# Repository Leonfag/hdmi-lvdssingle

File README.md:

# hdmi-lvdssingle
single hdmi to lvds board based on watterotts approach

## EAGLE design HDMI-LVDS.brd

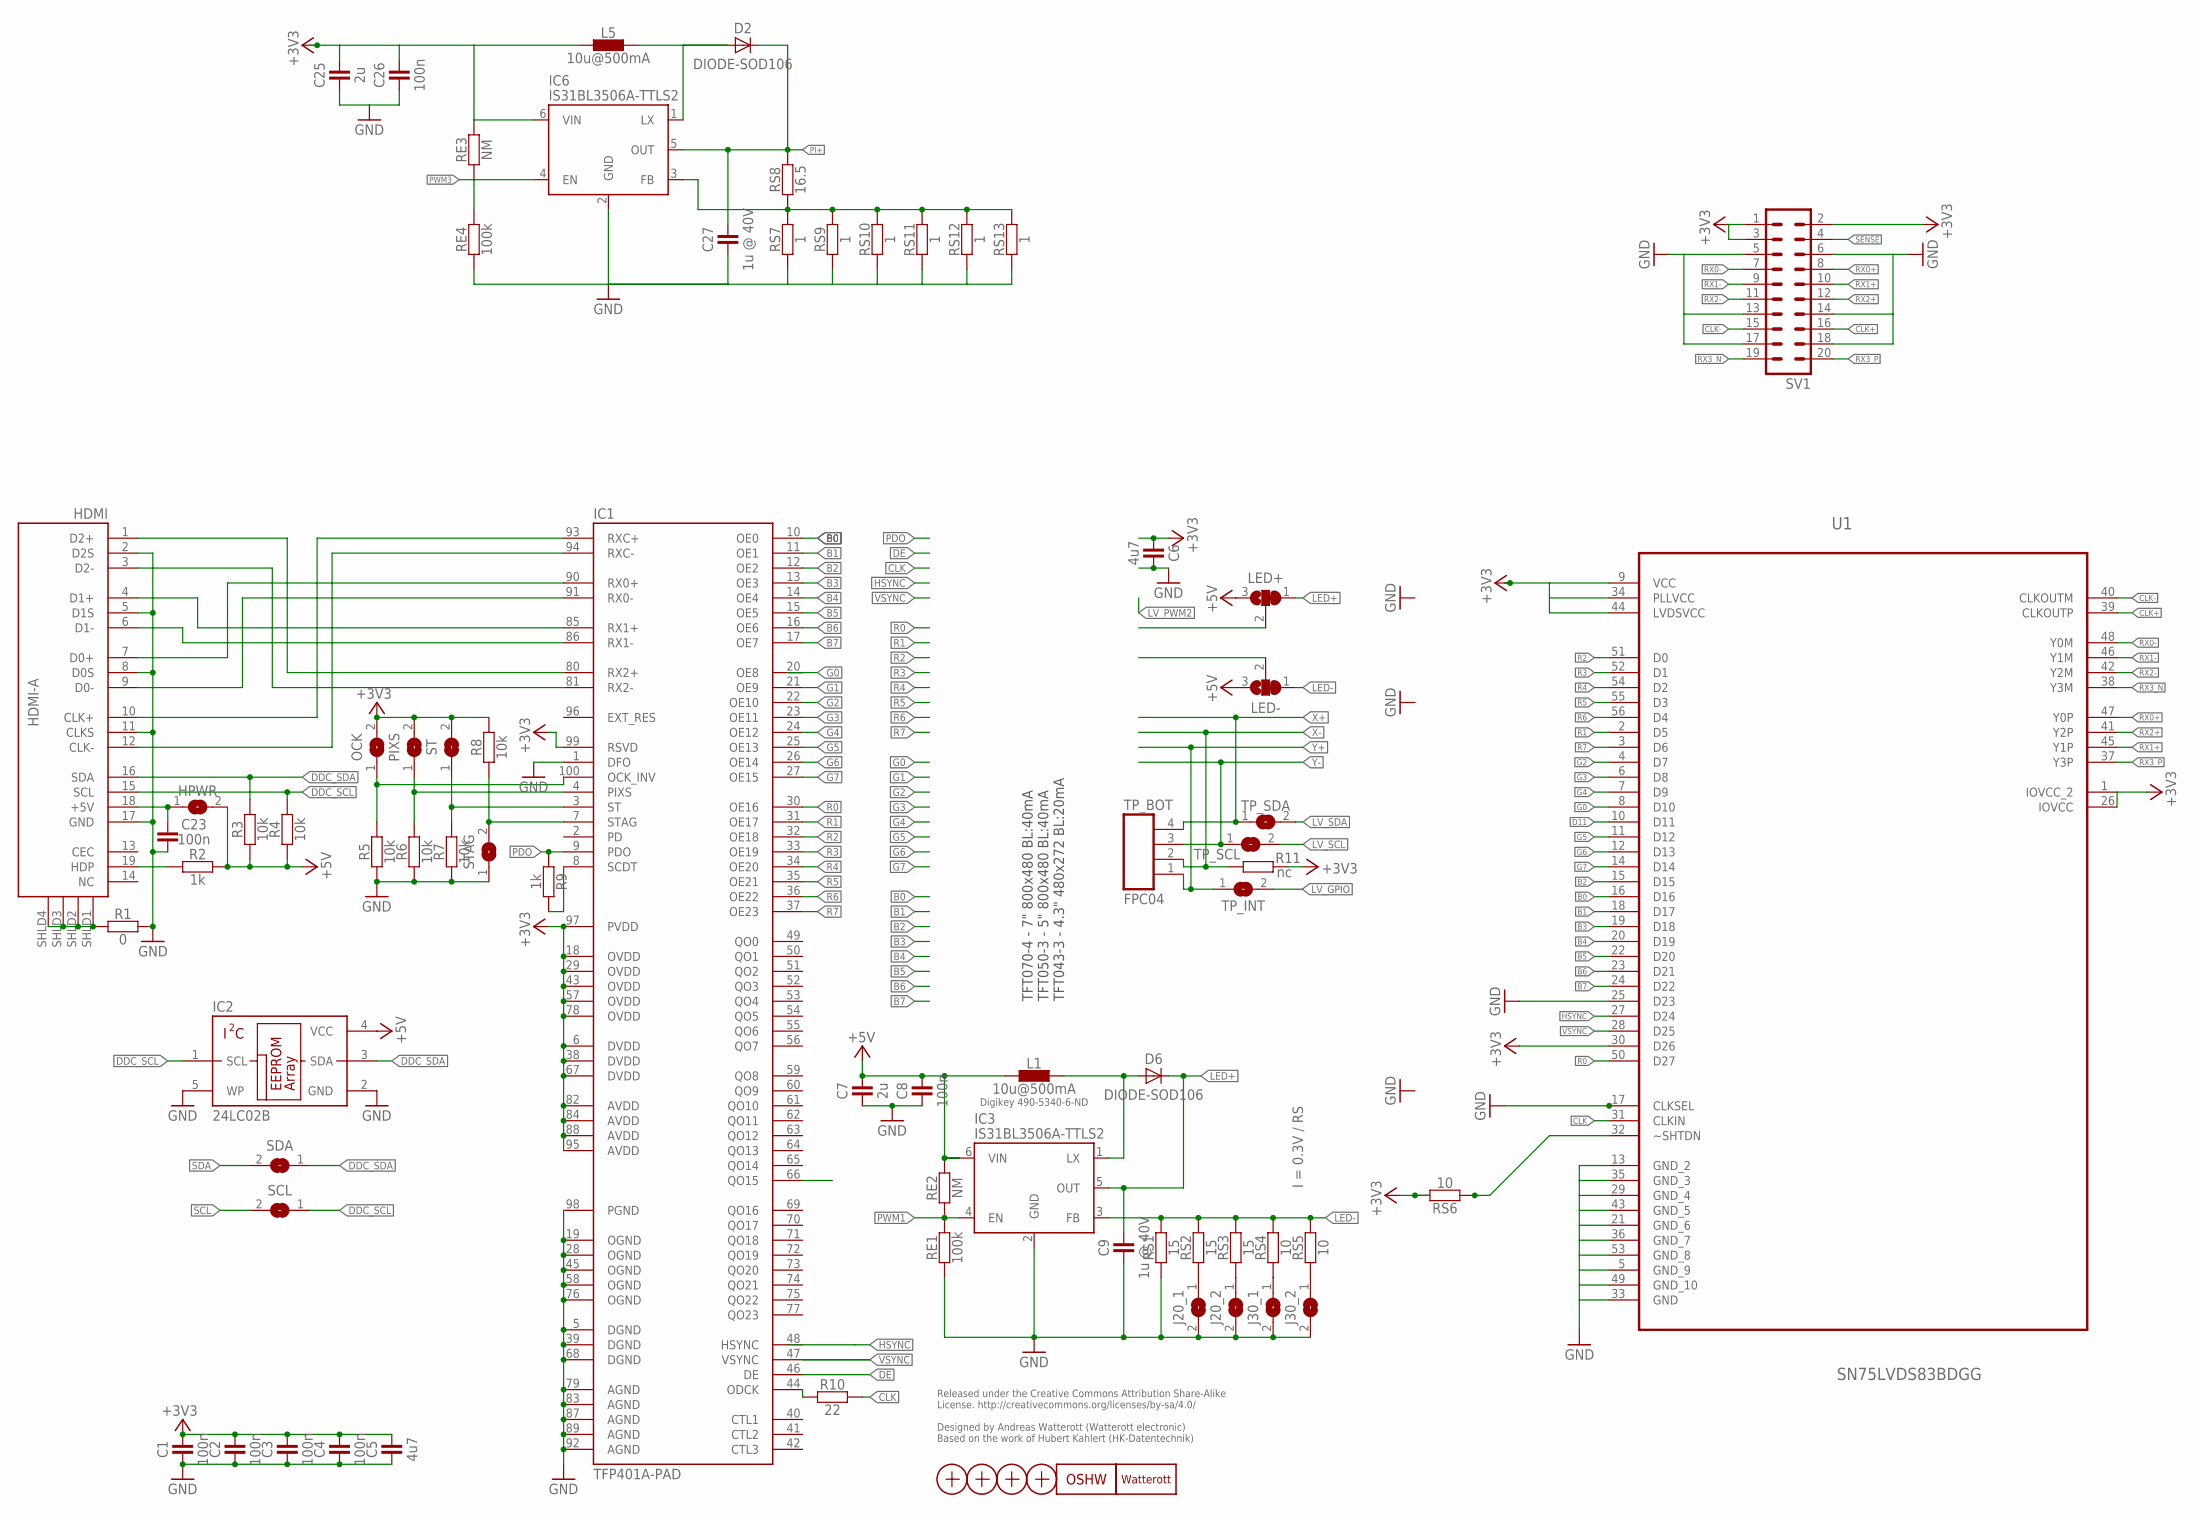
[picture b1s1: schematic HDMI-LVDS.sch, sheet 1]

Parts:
C1, C2, C3, C4, C8, C23, C26: 100n; C0402
C5, C6: 4u7; C0402
C7, C25: 2u; C0402
C9, C27: 1u @ 40V; C0805
D2, D6: DIODE-SOD106; SOD106
HDMI: HDMI-A; HDMI_10029449
HPWR: JUMPER2-0402
IC1: TFP401A-PAD; TQFP100-PAD
IC2: 24LC02B; SOT23-5
IC3, IC6: IS31BL3506A-TTLS2; SOT23-6
J20_1, J20_2, J30_1, J30_2: JUMPER2-0402
L1, L5: 10u@500mA; L_1212
LED+: JUMPER3-0402
LED-: JUMPER3-0402
LOGO1: OSHW_LOGOX0070; OSHW_6X70
LOGO3: LOGO-S_PLACE_S; SPARK_TPLACE_S
OCK: JUMPER2-0201-NC; JUMPER2-0201_NC
PIXS: JUMPER2-0201-NC; JUMPER2-0201_NC
R1: 0; C0402
R2, R9: 1k; C0402
R3, R4, R5, R6, R7, R8: 10k; C0402
R10: 22; C0402
R11: nc; C0402
RE1, RE4: 100k; C0402
RE2, RE3: NM; C0402
RS1, RS2, RS3: 15; C0402
RS4, RS5, RS6: 10; C0402
RS7, RS9, RS10, RS11, RS12, RS13: 1; C0402
RS8: 16.5; C0402
SCL: JUMPER2-0402
SDA: JUMPER2-0402
ST: JUMPER2-0201-NC; JUMPER2-0201_NC
STAG: JUMPER2-0201-NC; JUMPER2-0201_NC
SV1: MA10-2
TP_BOT: FPC04
TP_INT: JUMPER2-0402
TP_SCL: JUMPER2-0402
TP_SDA: JUMPER2-0402
U1: SN75LVDS83BDGG; SOP50P810X120-56N
X1, X2, X3, X4: PASSER-07; PASSER_07MM

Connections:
+3V3: C1.2, C2.2, C3.2, C4.2, C5.2, C6.1, C25.2, C26.2, IC1.6 (DVDD), IC1.18 (OVDD), IC1.29 (OVDD), IC1.38 (DVDD), IC1.43 (OVDD), IC1.57 (OVDD), IC1.67 (DVDD), IC1.78 (OVDD), IC1.82 (AVDD), IC1.84 (AVDD), IC1.88 (AVDD), IC1.95 (AVDD), IC1.97 (PVDD), IC1.99 (RSVD), IC6.6 (VIN), L5.1, OCK.2, PIXS.2, R8.2, R11.2, RE3.2, RS6.2, ST.2, SV1.1, SV1.2, SV1.3, U1.1 (IOVCC_2), U1.9 (VCC), U1.26 (IOVCC), U1.30 (D26), U1.34 (PLLVCC), U1.44 (LVDSVCC); also elsewhere on the board
+5V: C7.2, C8.2, HPWR.2, IC2.4 (VCC), IC3.6 (VIN), L1.1, LED+.3, LED-.3, R2.2, R3.1, R4.1, RE2.2; also elsewhere on the board
B0: IC1.10 (OE0), U1.16 (D16)
B1: IC1.11 (OE1), U1.18 (D17)
B2: IC1.12 (OE2), U1.15 (D15)
B3: IC1.13 (OE3), U1.19 (D18)
B4: IC1.14 (OE4), U1.20 (D19)
B5: IC1.15 (OE5), U1.22 (D20)
B6: IC1.16 (OE6), U1.23 (D21)
B7: IC1.17 (OE7), U1.24 (D22)
CLK: R10.2, U1.31 (CLKIN)
CLK+: SV1.16, U1.39 (CLKOUTP)
CLK-: SV1.15, U1.40 (CLKOUTM)
CLK_N: HDMI.12 (CLK-), IC1.94 (RXC-)
CLK_P: HDMI.10 (CLK+), IC1.93 (RXC+)
D0_N: HDMI.9 (D0-), IC1.91 (RX0-)
D0_P: HDMI.7 (D0+), IC1.90 (RX0+)
D1_N: HDMI.6 (D1-), IC1.86 (RX1-)
D1_P: HDMI.4 (D1+), IC1.85 (RX1+)
D2_N: HDMI.3 (D2-), IC1.81 (RX2-)
D2_P: HDMI.1 (D2+), IC1.80 (RX2+)
D11: U1.10 (D11)
DDC_SCL: HDMI.15 (SCL), IC2.1 (SCL), R4.2, SCL.1
DDC_SDA: HDMI.16 (SDA), IC2.3 (SDA), R3.2, SDA.1
DE: IC1.46 (DE)
G0: IC1.20 (OE8), U1.8 (D10)
G1: IC1.21 (OE9)
G2: IC1.22 (OE10), U1.4 (D7)
G3: IC1.23 (OE11), U1.6 (D8)
G4: IC1.24 (OE12), U1.7 (D9)
G5: IC1.25 (OE13), U1.11 (D12)
G6: IC1.26 (OE14), U1.12 (D13)
G7: IC1.27 (OE15), U1.14 (D14)
GND: C1.1, C2.1, C3.1, C4.1, C5.1, C6.2, C7.1, C8.1, C9.1, C23.1, C25.1, C26.1, C27.1, HDMI.2 (D2S), HDMI.5 (D1S), HDMI.8 (D0S), HDMI.11 (CLKS), HDMI.17 (GND), IC1.1 (DFO), IC1.5 (DGND), IC1.19 (OGND), IC1.28 (OGND), IC1.39 (DGND), IC1.45 (OGND), IC1.58 (OGND), IC1.68 (DGND), IC1.76 (OGND), IC1.79 (AGND), IC1.83 (AGND), IC1.87 (AGND), IC1.89 (AGND), IC1.92 (AGND), IC1.98 (PGND), IC2.2 (GND), IC2.5 (WP), IC3.2 (GND), IC6.2 (GND), J20_1.2, J20_2.2, J30_1.2, J30_2.2, R1.1, R5.1, R6.1, R7.1, RE1.1, RE4.1, RS1.1, RS7.1, RS9.1, RS10.1, RS11.1, RS12.1, RS13.1, STAG.1, SV1.5, SV1.6, SV1.13, SV1.14, SV1.17, SV1.18, U1.5 (GND_9), U1.13 (GND_2), U1.21 (GND_6), U1.25 (D23), U1.29 (GND_4), U1.33 (GND), U1.35 (GND_3), U1.36 (GND_7), U1.43 (GND_5), U1.49 (GND_10), U1.53 (GND_8); also elsewhere on the board
HDMI_5V: C23.2, HDMI.18 (+5V), HPWR.1
HDMI_DECT: HDMI.19 (HDP), R2.1
HSYNC: IC1.48 (HSYNC), U1.27 (D24)
LED+: C9.2, D6.C, IC3.5 (OUT), LED+.1
LED-: IC3.3 (FB), LED-.1, RS1.2, RS2.2, RS3.2, RS4.2, RS5.2
LEDA: LED+.2
LEDC: LED-.2
LV_GPIO: TP_INT.2; also elsewhere on the board
LV_SCL: TP_SCL.2; also elsewhere on the board
LV_SDA: TP_SDA.2; also elsewhere on the board
LX: D6.A, IC3.1 (LX), L1.2
unnamed: J20_2.1, RS3.1
unnamed: IC1.44 (ODCK), R10.1
unnamed: J30_1.1, RS4.1
unnamed: J20_1.1, RS2.1
unnamed: J30_2.1, RS5.1
unnamed: IC6.3 (FB), RS7.2, RS8.1, RS9.2, RS10.2, RS11.2, RS12.2, RS13.2
unnamed: RS6.1, U1.32 (~SHTDN)
unnamed: D2.A, IC6.1 (LX), L5.2
OCKINV: IC1.100 (OCK_INV), OCK.1, R5.2
PDO: IC1.9 (PDO), R9.1
PI+: C27.2, D2.C, IC6.5 (OUT), RS8.2; also elsewhere on the board
PIXS: IC1.4 (PIXS), PIXS.1, R6.2
PWM1: IC3.4 (EN), RE1.2, RE2.1; also elsewhere on the board
PWM3: IC6.4 (EN), RE3.1, RE4.2; also elsewhere on the board
R0: IC1.30 (OE16), U1.50 (D27)
R1: IC1.31 (OE17), U1.2 (D5)
R2: IC1.32 (OE18), U1.51 (D0)
R3: IC1.33 (OE19), U1.52 (D1)
R4: IC1.34 (OE20), U1.54 (D2)
R5: IC1.35 (OE21), U1.55 (D3)
R6: IC1.36 (OE22), U1.56 (D4)
R7: IC1.37 (OE23), U1.3 (D6)
RX0+: SV1.8, U1.47 (Y0P)
RX0-: SV1.7, U1.48 (Y0M)
RX1+: SV1.10, U1.45 (Y1P)
RX1-: SV1.9, U1.46 (Y1M)
RX2+: SV1.12, U1.41 (Y2P)
RX2-: SV1.11, U1.42 (Y2M)
RX3_N: SV1.19, U1.38 (Y3M)
RX3_P: SV1.20, U1.37 (Y3P)
SCDT: IC1.8 (SCDT), R9.2
SCL: SCL.2; also elsewhere on the board
SDA: SDA.2; also elsewhere on the board
SENSE: SV1.4; also elsewhere on the board
SHLD3: HDMI.SHLD1 (SHLD), HDMI.SHLD2 (SHLD), HDMI.SHLD3 (SHLD), HDMI.SHLD4 (SHLD), R1.2
ST: IC1.3 (ST), R7.2, ST.1
STAG: IC1.7 (STAG), R8.1, STAG.2
VSYNC: IC1.47 (VSYNC), U1.28 (D25)
X+: TP_BOT.4, TP_SDA.1; also elsewhere on the board
X-: R11.1, TP_BOT.2; also elsewhere on the board
Y+: TP_BOT.1, TP_INT.1; also elsewhere on the board
Y-: TP_BOT.3, TP_SCL.1; also elsewhere on the board

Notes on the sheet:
I = 0.3V / RS
Digikey 490-5340-6-ND
Released under the Creative Commons Attribution Share-Alike License. http://creativecommons.org/licenses/by-sa/4.0/ Designed by Andreas Watterott (Watterott electronic) Based on the work of Hubert Kahlert (HK-Datentechnik)
TFT070-4 - 7" 800x480 BL:40mA TFT050-3 - 5" 800x480 BL:40mA TFT043-3 - 4.3" 480x272 BL:20mA

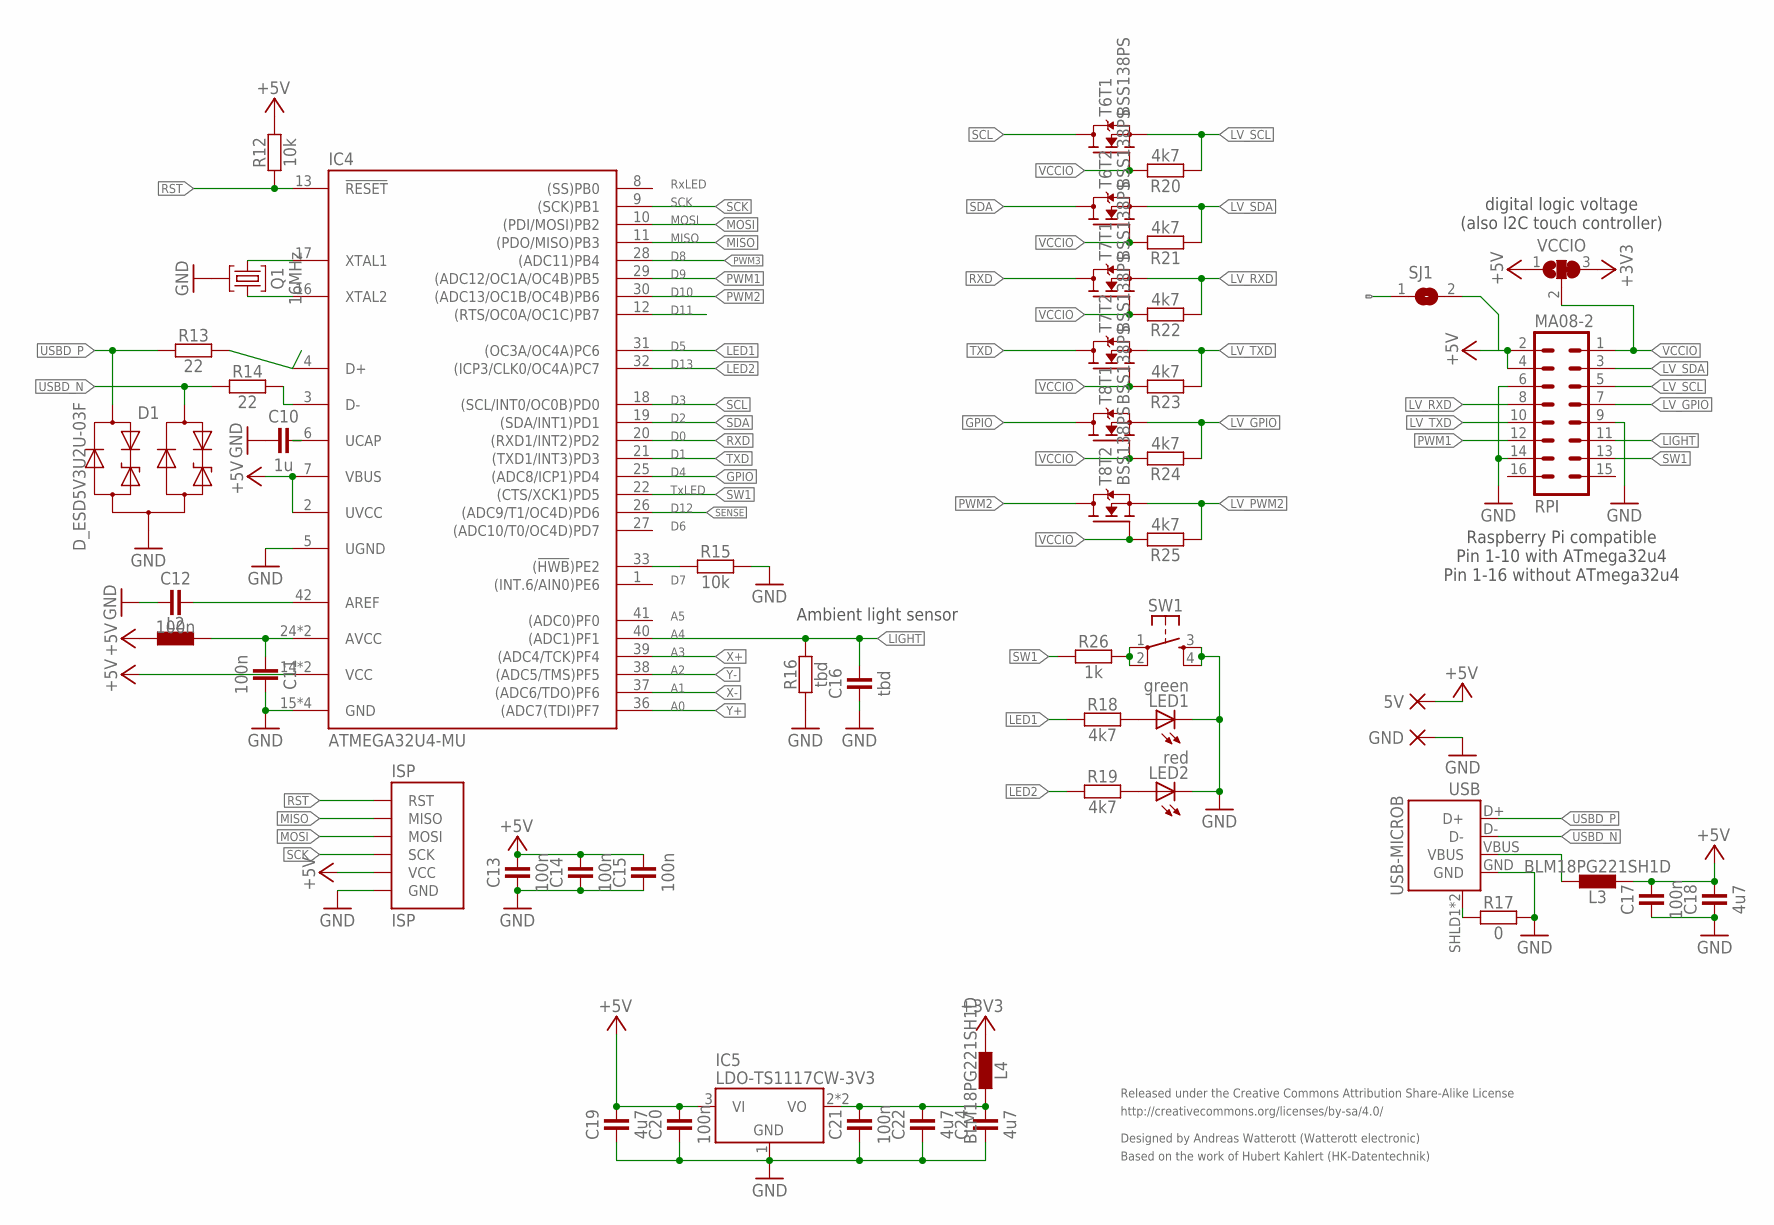
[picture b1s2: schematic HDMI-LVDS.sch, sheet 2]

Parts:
5V: PAD-1.27X2.54_NC
C10: 1u; C0402
C11, C12, C13, C14, C15, C17, C20, C21: 100n; C0402
C16: tbd; C0402
C18, C19, C22, C24: 4u7; C0402
D1: D_ESD5V3U2U-03F; SOT723
GND: PAD-1.27X2.54_NC
IC4: ATMEGA32U4-MU; QFN44
IC5: LDO-TS1117CW-3V3; SOT223
ISP: ISP; ISP-2X3
L2: INDUCTOR-0603; C0603
L3, L4: BLM18PG221SH1D; C0603
LED1: green; C0603
LED2: red; C0603
Q1: 16MHz; CRYSTAL_32X13
R12, R15: 10k; C0402
R13, R14: 22; C0402
R16: tbd; C0402
R17: 0; C0402
R18, R19, R20, R21, R22, R23, R24, R25: 4k7; C0402
R26: 1k; C0402
RPI: MA08-2
SJ1: SJ
SW1: SW-TACTILE-PTS840P; PTS840P
T6, T7, T8: BSS138PS; SOT363
USB: USB-MICROB; USB-MICROB-10103594
VCCIO: JUMPER3-0402

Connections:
3VOUT: C21.2, C22.2, C24.2, IC5.2 (VO), IC5.4 (VO), L4.2
+3V3: L4.1, VCCIO.3; also elsewhere on the board
+5V: 5V.1, C13.2, C14.2, C15.2, C17.2, C18.2, C19.2, C20.2, IC4.2 (UVCC), IC4.7 (VBUS), IC4.14 (VCC), IC4.34 (VCC), IC5.3 (VI), ISP.VCC, L2.1, L3.1, R12.2, RPI.2, RPI.4, SJ1.2, VCCIO.1; also elsewhere on the board
AREF: C12.2, IC4.42 (AREF)
AVCC: C11.1, IC4.24 (AVCC), IC4.44 (AVCC), L2.2
D_N: IC4.3 (D-), R14.2
D_P: IC4.4 (D+), R13.2
GND: C10.1, C11.2, C12.1, C13.1, C14.1, C15.1, C16.1, C17.1, C18.1, C19.1, C20.1, C21.1, C22.1, C24.1, D1.3 (A), GND.1, IC4.5 (UGND), IC4.15 (GND), IC4.23 (GND), IC4.35 (GND), IC4.43 (GND), IC5.1 (GND), ISP.GND, LED1.C, LED2.C, Q1.GND, R15.2, R16.1, R17.1, RPI.6, RPI.9, RPI.14, SW1.3 (S1), SW1.4 (S2), USB.GND; also elsewhere on the board
GPIO: IC4.25 ((ADC8/ICP1)PD4), T8.6 (D)
HWB: IC4.33 ((!HWB!)PE2), R15.1
LED1: IC4.31 ((OC3A/OC4A)PC6), R18.1
LED2: IC4.32 ((ICP3/CLK0/OC4A)PC7), R19.1
LIGHT: C16.2, IC4.40 ((ADC1)PF1), R16.2, RPI.11
LV_GPIO: R24.1, RPI.7, T8.1 (S); also elsewhere on the board
LV_PWM2: R25.1, T8.4 (S)
LV_RXD: R22.1, RPI.8, T7.1 (S)
LV_SCL: R20.1, RPI.5, T6.1 (S); also elsewhere on the board
LV_SDA: R21.1, RPI.3, T6.4 (S); also elsewhere on the board
LV_TXD: R23.1, RPI.10, T7.4 (S)
MISO: IC4.11 ((PDO/MISO)PB3), ISP.MISO
MOSI: IC4.10 ((PDI/MOSI)PB2), ISP.MOSI
unnamed: R26.2, SW1.1, SW1.2
unnamed: LED1.A, R18.2
unnamed: LED2.A, R19.2
PI+: SJ1.1; also elsewhere on the board
PWM1: IC4.29 ((ADC12/OC1A/OC4B)PB5), RPI.12; also elsewhere on the board
PWM2: IC4.30 ((ADC13/OC1B/OC4B)PB6), T8.3 (D)
PWM3: IC4.28 ((ADC11)PB4); also elsewhere on the board
RST: IC4.13 (!RESET), ISP.RST, R12.1
RXD: IC4.20 ((RXD1/INT2)PD2), T7.6 (D)
SCK: IC4.9 ((SCK)PB1), ISP.SCK
SCL: IC4.18 ((SCL/INT0/OC0B)PD0), T6.6 (D); also elsewhere on the board
SDA: IC4.19 ((SDA/INT1)PD1), T6.3 (D); also elsewhere on the board
SENSE: IC4.26 ((ADC9/T1/OC4D)PD6); also elsewhere on the board
SHLD1: R17.2, USB.SHLD1 (SHIELD), USB.SHLD2 (SHIELD)
SW1: IC4.22 ((CTS/XCK1)PD5), R26.1, RPI.13
TXD: IC4.21 ((TXD1/INT3)PD3), T7.3 (D)
UCAP: C10.2, IC4.6 (UCAP)
USBD_N: D1.2 (C2), R14.1, USB.D-
USBD_P: D1.1 (C1), R13.1, USB.D+
VBUS: L3.2, USB.VBUS
VCCIO: R20.2, R21.2, R22.2, R23.2, R24.2, R25.2, RPI.1, T6.2 (G), T6.5 (G), T7.2 (G), T7.5 (G), T8.2 (G), T8.5 (G), VCCIO.2
X+: IC4.39 ((ADC4/TCK)PF4); also elsewhere on the board
X-: IC4.37 ((ADC6/TDO)PF6); also elsewhere on the board
XTAL1: IC4.17 (XTAL1), Q1.2
XTAL2: IC4.16 (XTAL2), Q1.1
Y+: IC4.36 ((ADC7(TDI)PF7); also elsewhere on the board
Y-: IC4.38 ((ADC5/TMS)PF5); also elsewhere on the board

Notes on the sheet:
Ambient light sensor
Released under the Creative Commons Attribution Share-Alike License
http://creativecommons.org/licenses/by-sa/4.0/
Designed by Andreas Watterott (Watterott electronic)
Based on the work of Hubert Kahlert (HK-Datentechnik)
TxLED
D12
D13
RxLED
SCK
MOSI
MISO
D10
D11
Raspberry Pi compatible Pin 1-10 with ATmega32u4 Pin 1-16 without ATmega32u4
digital logic voltage (also I2C touch controller)

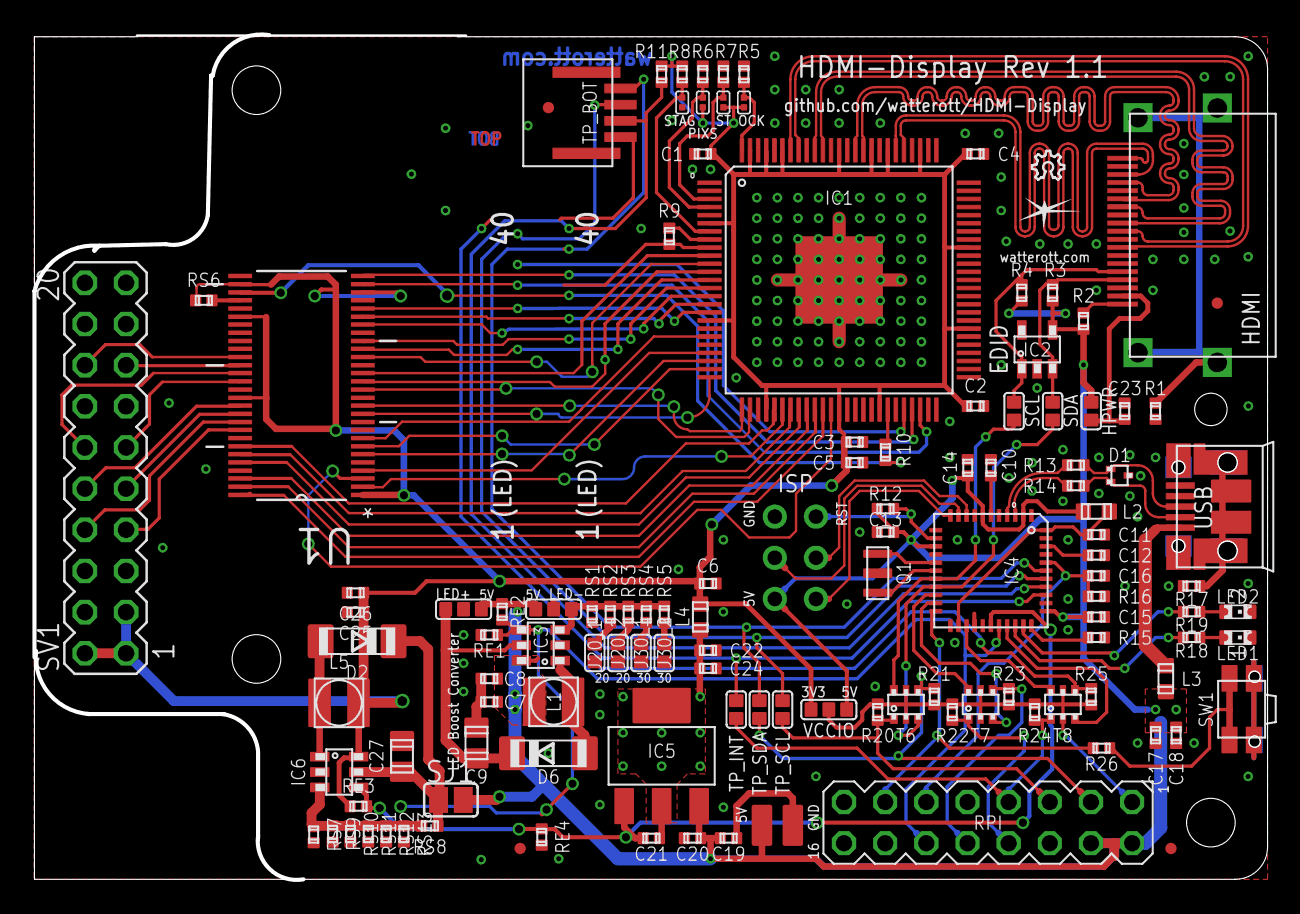
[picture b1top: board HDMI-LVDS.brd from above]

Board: 2 copper layers, 76.1 x 52.2 mm, 124 parts (0 on the bottom side), 114 nets.

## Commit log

2016-09-15 source files for hardware desigm
